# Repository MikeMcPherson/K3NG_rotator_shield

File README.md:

# K3NG_rotator_shield

This simple azimuth interface Arduino shield implements the minimal drivers and filtering for interfacing a K3NG rotator controller (https://blog.radioartisan.com/yaesu-rotator-computer-serial-interface/) to a Yaesu G-800DXA using the example circuit diagram from K3NG's documentation.  The shield has two drivers for the CW and CCW lines, one low-pass RC filter to smooth the PWM output that drives the speed line, and one input that senses the azimuth voltage from the Yaesu controller.  It also has a reset button for the Arduino, since the button on the Arduino gets covered by the shield.

I ordered the boards from JLCPCB and the components from Digi-Key, but the components are standard and the Gerbers should work anywhere.

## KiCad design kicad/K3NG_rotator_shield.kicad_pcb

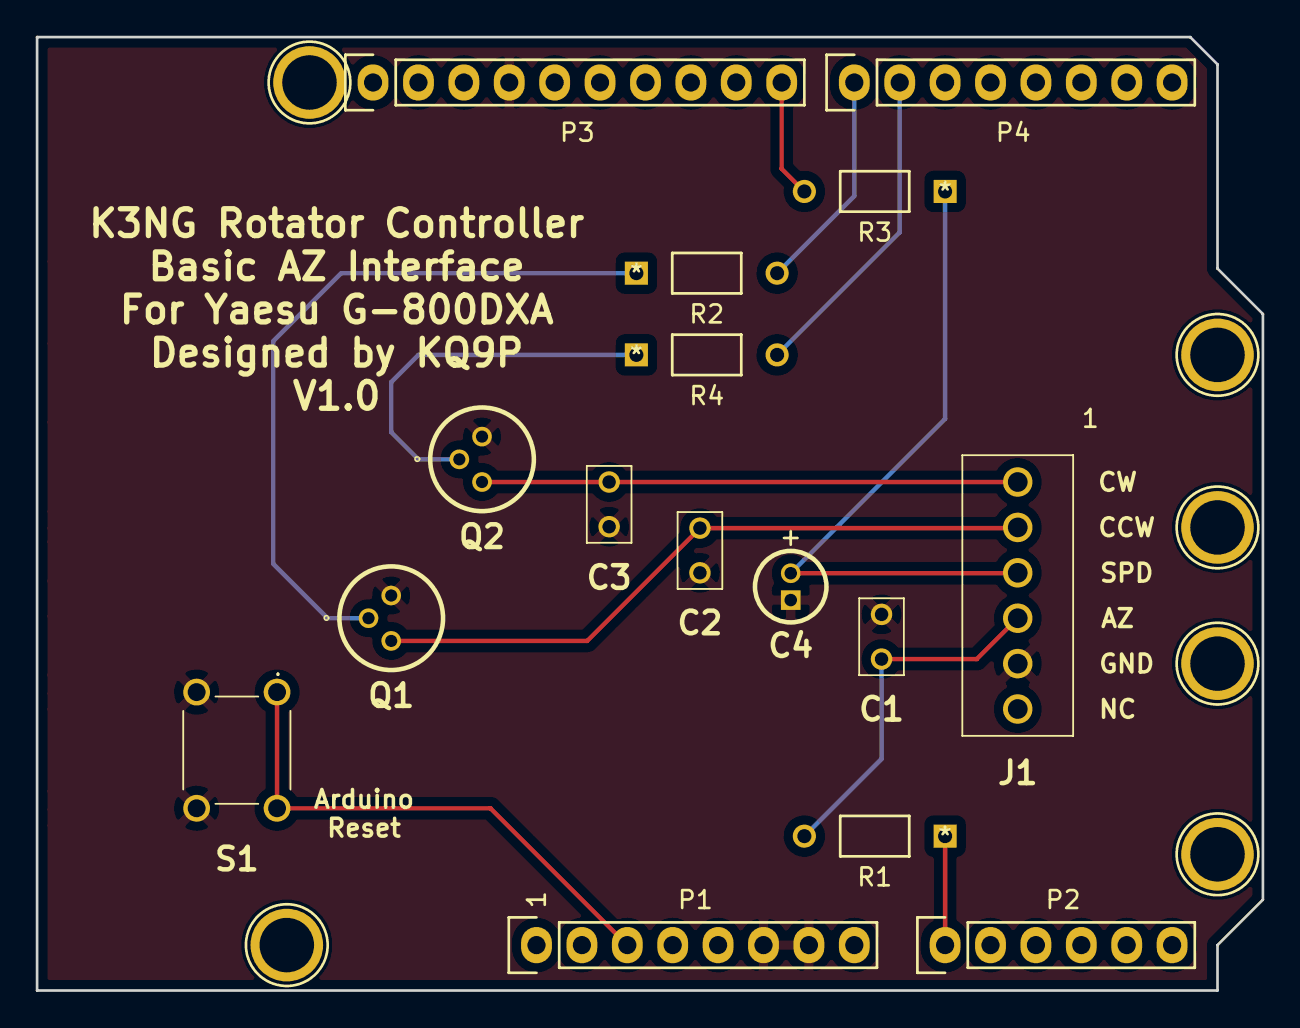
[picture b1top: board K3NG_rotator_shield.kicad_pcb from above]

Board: 2 copper layers, 68.6 x 53.3 mm, 22 parts (0 on the bottom side), 13 nets.

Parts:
C1, C2, C3: RDER71H103K0M1H03A; RCE5C1H103J1A2H03B
C4: EEA-GA1E100B; CAPPRD150W50D400H800
J1: Screw_Terminal_01x06; 1725698
P1: Power; Socket_Strip_Arduino_1x08
P2: Analog; Socket_Strip_Arduino_1x06
P3: Digital; Socket_Strip_Arduino_1x10
P4: Digital; Socket_Strip_Arduino_1x08
P5, P6, P7, P8, P8#2, P8#3: CONN_01X01; Arduino_1pin
Q1, Q2: 2N2222A; TO-18_4
R1, R2, R4: CFM14JT1K00
R3: CFM14JT4K70
S1: 1825967-2; 18259672

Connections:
/6(**): P4.2, R4.2
/7: P4.1, R2.2
/8: P3.10, R3.2
/A0: P2.1, R1.1
/AZctlr: C1.1, J1.4, R1.2
/CCWctlr: C2.2, J1.2, Q1.2
/CWctlr: C3.1, J1.1, Q2.2
/Reset: P1.3, S1.1, S1.2
/SPDctlr: C4.2, J1.3, R3.1
GND: C1.2, C2.1, C3.2, C4.1, J1.5, P1.6, P1.7, P3.4, Q1.3, Q2.3, S1.3, S1.4
unnamed: P8.1, P8#2.1, P8#3.1
unnamed: Q1.1, R2.1
unnamed: Q2.1, R4.1

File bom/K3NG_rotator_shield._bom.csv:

Item,References,Value,Quantity
1,C4,EEA-GA1E100B,1
2,"C1, C2, C3",RDER71H103K0M1H03A,3
3,"R1, R2, R4",CFM14JT1K00,3
4,R3,CFM14JT4K70,1
5,S1,1825967-2,1
6,"Q1, Q2",2368-2N2222A-ND,2
7,J1,1725698,1
8,"P1, P2, P3, P4",LS-00010,1

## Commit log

2021-02-16 Init repo
2021-02-16 Initial schematic
2021-02-18 Ready for final proofread
2021-02-19 Part selection and layout complete
2021-02-19 Fixed mistakes, generated Gerbers, ordered
2021-03-05 Final version, tested and complete
2021-03-05 Organize and document
2021-03-05 Fix typo
2021-03-05 Add BOM
2021-03-05 Cleanup
2021-03-05 Added PDF of schematic and edited README.

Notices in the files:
parts and their libraries:
Copyright 2016 Accelerated Designs. All rights reserved.
